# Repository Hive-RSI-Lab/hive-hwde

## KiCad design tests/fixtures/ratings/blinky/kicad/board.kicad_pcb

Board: 0 copper layers, 20 parts (0 on the bottom side), 12 nets, no tracks yet.

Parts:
C1, C2, C3, C9: 100nF 50V X7R; C0603
C4: 1uF 50V X5R; C0603
C5: 22uF 16V tantalum; CASE-B_3528
C6, C11: 10uF 25V X5R; C0805
C7, C8: 22pF 50V C0G; C0603
C10: 10nF 50V X7R; C0603
D1: SS34; SMA_L4.3-W2.6-LS5.2-RD
D2: Red 0805; LED0805-RD
J1: 1x2 2.54mm male THT; HDR-TH_2P-P2.54-V-M-3
J2: 1x4 2.54mm male THT; HDR-TH_4P-P2.54-V-M
R1: 1k; R0603
R2: 10k; R0603
U1: STM32F103C8T6; LQFP-48_L7.0-W7.0-P0.50-LS9.0-BL
U2: AMS1117-3.3; SOT-223-3_L6.5-W3.4-P2.30-LS7.0-BR
Y1: 8MHz 20pF; CRYSTAL-SMD_L11.5-W4.8-LS12.7

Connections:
+3V3: C1.1, C2.1, C3.1, C4.1, C5.1, C10.1, C11.1, J2.3, R1.1, U1.1, U1.9, U1.24, U1.36, U1.48, U2.2, U2.4
+5V: C6.1, D1.1, U2.3
/BOOT0: R2.1, U1.44
/LED: D2.1, U1.2
/LED_A: D2.2, R1.2
/NRST: C9.1, U1.7
/OSC_IN: C7.1, U1.5, Y1.1
/OSC_OUT: C8.1, U1.6, Y1.2
/SWCLK: J2.2, U1.37
/SWDIO: J2.1, U1.34
/VIN: D1.2, J1.1
GND: C1.2, C2.2, C3.2, C4.2, C5.2, C6.2, C7.2, C8.2, C9.2, C10.2, C11.2, J1.2, J2.4, R2.2, U1.8, U1.23, U1.35, U1.47, U2.1

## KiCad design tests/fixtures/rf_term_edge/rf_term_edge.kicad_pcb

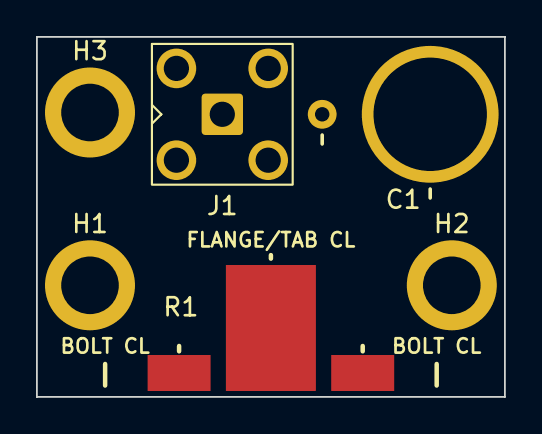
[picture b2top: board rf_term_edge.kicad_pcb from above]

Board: 2 copper layers, 26.0 x 20.0 mm, 6 parts (0 on the bottom side), 2 nets, no tracks yet.

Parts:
C1: 1-30pF; CAP-ADJ-TH_2P-BD7.5_5602
H1, H2, H3: M3; MountingHole_3.2mm_M3_Pad_5.0mm
J1: SMA; SMA_BAT_Wireless_BWSMA-KWE-Z001
R1: 50R 250W; R_LapPad_T50R0-250-12X

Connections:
/RF: C1.2, J1.1, R1.1
GND: C1.1, H1.1, H2.1, H3.1, J1.2, R1.2

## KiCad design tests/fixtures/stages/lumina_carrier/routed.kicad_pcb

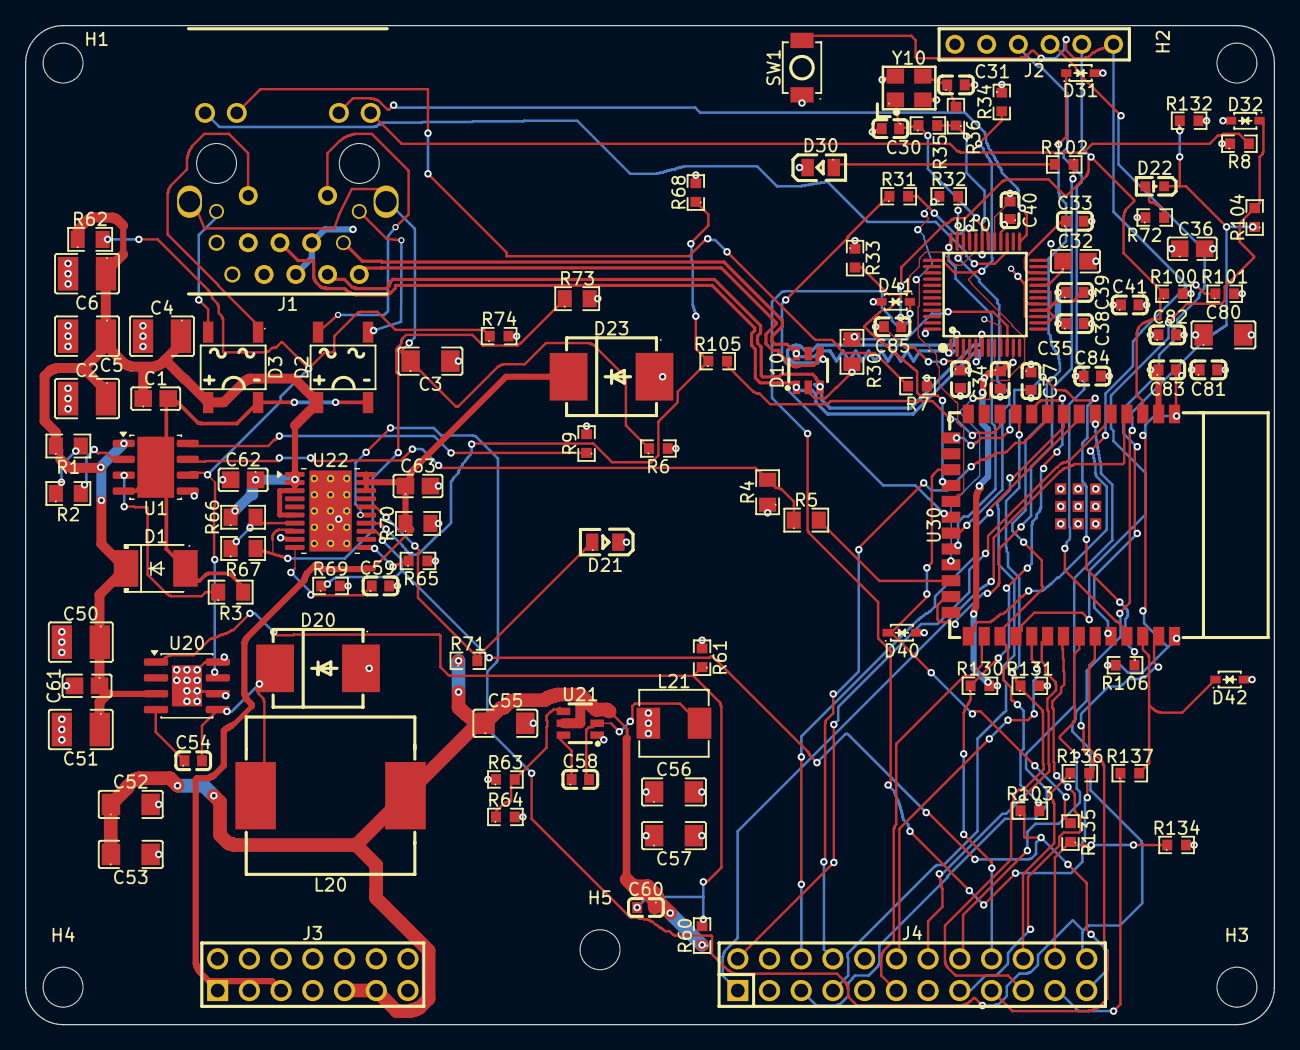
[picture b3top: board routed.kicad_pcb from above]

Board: 4 copper layers, 100.0 x 80.0 mm, 116 parts (0 on the bottom side), 85 nets.

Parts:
C1, C61, C62, C63: 100nF 100V X7R 0805; C0805
C2, C4, C5, C6: 10uF 100V X7R 1210; C1210
C3: 1nF 2kV X7R 1206; C1206
C30, C31: 27pF 50V NP0 0603; C0603
C32, C36: 4.7uF 25V X5R 0805; C0805
C33, C59: 10nF 50V X7R 0603; C0603
C34, C35, C37, C38, C39, C40, C41, C54, C58: 100nF 50V X7R 0603; C0603
C50, C51: 2.2uF 100V X7R 1210; C1210
C52, C53, C55, C56, C57: 22uF 25V X5R 1206; C1206
C60: 150pF 50V NP0 0603; C0603
C80: 22uF 25V X5R; C1206
C81, C82, C83: 100nF 50V X7R; C0603
C84, C85: 1uF 50V X5R; C0603
D1: SMBJ58A 58V 600W TVS; SMB_L4.3-W3.6-LS5.4-R-RD
D2: ABS210 2A 1000V bridge (Alt A); ABF_L5.1-W4.4-P4.00-LS6.2-BL
D3: ABS210 2A 1000V bridge (Alt B); ABF_L5.1-W4.4-P4.00-LS6.2-BL
D10: TPD4E1U06 4ch 0.55pF ESD array; SOT-23-6_L2.9-W1.6-P0.95-LS2.8-BR
D20, D23: SS510C 100V 5A Schottky SMC; SMC_L7.1-W6.2-LS8.1-R-RD
D21, D30: Green LED 0805; LED0805-R-RD
D22: Red LED 0603; LED-SMD_L1.6-W0.8-R-RD
D31, D32, D40, D41, D42: PESD3V3L1BA 3.3V ESD clamp SOD-323; SOD-323_L1.7-W1.3-LS2.6-BI
H1, H2, H3, H4, H5: MountingHole_3.2mm_M3
J1: LPJG0926HENL PoE+ RJ45 magjack; RJ45-TH_LPJG0926HENL_C22457393
J2: 1x6 2.54mm header (recovery); CONN-TH_DS1021-1X6SF11-B
J3: DS1021-2x7SF11-B 2x7 male header; HDR-TH_14P-P2.54-V-M-R2-C7-S2.54-1
J4: DS1021-2x12SF11-B 2x12 male header; HDR-TH_24P-P2.54-V-M-R2-C12-S2.54
L20: 68uH 3A 140mohm inductor; IND-SMD_L12.6-W13.5
L21: 4.7uH 4A 46mohm inductor; IND-SMD_L5.4-W5.2
R1, R2: 12.1k 1% 0805; R0805
R3: 90.9R 1% 0805; R0805
R4, R5: 10k 1% 0805; R0805
R6, R35: 1M 1% 0603; R0603
R7, R8, R72: 330R 1% 0603; R0603
R9, R36: 0R jumper 0603; R0603
R30: 12.4k 1% 0805; R0805
R31, R32: 22R 1% 0603; R0603
R33, R34, R64, R69, R71, R106, R132, R134: 10k 1% 0603; R0603
R60: 270k 1% 0603; R0603
R61, R68: 30k 1% 0603; R0603
R62, R70: 100k 1% 0805; R0805
R63: 33k 1% 0603; R0603
R65: 18k 1% 0603; R0603
R66: 620k 0.1% 0805; R0805
R67: 10k 0.1% 0805; R0805
R73: 12k 0.1% 0805; R0805
R74, R130, R131: 4.7k 1% 0603; R0603
R100, R101: 10k; R0603
R102: 330R; R0603
R103, R104, R105, R135, R136, R137: 1k 1% 0603; R0603
SW1: SMD tactile switch; SW-SMD_L3.9-W3.0-P4.45
U1: TPS2378DDAR; SOIC-8-1EP_3.9x4.9mm_P1.27mm_EP2.95x4.9mm_Mask2.71x3.4mm
U10: W5500; LQFP-48_L7.0-W7.0-P0.50-LS9.0-BL
U20: SCT2A25STER; SOIC-8-1EP_3.9x4.9mm_P1.27mm_EP2.41x3.3mm
U21: TPS563201DDCR; SOT-23-6_L2.9-W1.6-P0.95-LS2.8-BR
U22: TPS16630PWPR; HTSSOP-20-1EP_4.4x6.5mm_P0.65mm_EP3.4x6.5mm_Mask2.96x2.96mm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
U30: ESP32-S3-WROOM-1-N8; WIFIM-SMD_ESP32-S3-WROOM-1-N8
Y10: 25MHz 18pF CL crystal; OSC-SMD_4P-L3.2-W2.5-BL_SIT8008BI

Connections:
+3V3: C34.1, C35.1, C36.1, C37.1, C38.1, C39.1, C40.1, C41.1, C56.1, C57.1, C80.1, C81.1, C82.1, C83.1, C84.1, J1.4, J1.5, J2.2, J3.12, J3.14, L21.2, R4.1, R7.1, R8.1, R33.1, R34.1, R63.1, R72.1, R100.2, R101.2, R130.2, R131.2, R132.2, R134.2, U10.4, U10.8, U10.11, U10.15, U10.17, U10.21, U10.28, U30.2
+12V: C52.1, C53.1, C55.1, C60.1, J3.9, J3.11, L20.2, R60.1, R71.1, U21.3, U21.5
+48V_SW: C63.1, D23.2, J3.1, J3.3, J3.5, R70.1, U22.18, U22.19, U22.20
/ADC0: D41.1, R136.2, U30.39
/ADC1: D42.1, R137.2, U30.38
/CDB: R62.2, R74.1, U1.6, U20.7
/DSPI_CSn: J4.17, U30.35
/DSPI_MISO: J4.16, U30.34
/DSPI_MOSI: J4.15, U30.33
/DSPI_SCK: J4.14, U30.32
/ENABLE: J4.23, R69.1, R103.1, U22.13
/ETH_CSn: R33.2, U10.32, U30.18
/ETH_INTn: U10.36, U30.22
/ETH_LED_ACT: J1.18, U10.27
/ETH_LED_LINK: J1.16, U10.25
/ETH_MISO: U10.34, U30.21
/ETH_MOSI: R32.1, U30.19
/ETH_RSTn: R34.2, U10.37, U30.23
/ETH_RXN: D10.1, J1.6, U10.5
/ETH_RXP: D10.3, J1.3, U10.6
/ETH_SCLK: R31.1, U30.20
/ETH_TXN: D10.6, J1.2, U10.1
/ETH_TXP: D10.4, J1.1, U10.2
/FAULT: D22.2, J4.24, R104.1, R132.1, U22.15
/I2C_SCL: J4.18, R130.1, U30.10
/I2C_SDA: J4.19, R131.1, U30.11
/ID_ADC: D40.1, R135.2, U30.17
/IMON: R68.1, R105.1, U22.14
/PWM0: J4.1, U30.4
/PWM1: J4.2, U30.5
/PWM2: J4.5, U30.6
/PWM3: J4.6, U30.7
/PWM4: J4.7, U30.8
/PWM5: J4.8, U30.9
/PWM6: J4.11, U30.28
/PWM7: J4.12, U30.31
/T2P: R5.2, U30.24
/eth/1V2O: C33.1, U10.22
/eth/EXRES: R30.1, U10.10
/eth/MOSI_PHY: R32.2, U10.35
/eth/SCLK_PHY: R31.2, U10.33
/eth/TOCAP: C32.1, U10.20
/eth/XI: C30.1, R35.1, U10.30, Y10.1
/eth/XO: R35.2, R36.1, U10.31
/eth/XO_XTAL: C31.1, R36.2, Y10.3
/expansion/ADC0_CONN: J4.20, R136.1
/expansion/ADC1_CONN: J4.21, R137.1
/expansion/ID_ADC_CONN: J4.22, R134.1, R135.1
/mcu/BOOT: J2.6, R101.1, SW1.1, U30.27
/mcu/EN: C85.1, J2.5, R100.1, U30.3
/mcu/ENABLE_M: D31.1, R103.2, U30.29
/mcu/FAULT_M: D32.1, R104.2, U30.30
/mcu/IMON_M: R105.2, U30.12
/mcu/IO3_STRAP: R106.1, U30.15
/mcu/RXD0: J2.4, U30.36
/mcu/STATUS: R102.1, U30.25
/mcu/STATUS_A: D30.1, R102.2
/mcu/TXD0: J2.3, U30.37
/poe/APD: R9.1, U1.8
/poe/CLS: R3.1, U1.3
/poe/DEN: R2.2, U1.2
/poe/DEN_TAP: R1.2, R2.1
/poe/LED_G_A: J1.15, R8.2
/poe/LED_Y_A: J1.17, R7.2
/poe/POE_TAP_A1: D2.1, J1.11
/poe/POE_TAP_A2: D2.2, J1.12
/poe/POE_TAP_B1: D3.1, J1.13
/poe/POE_TAP_B2: D3.2, J1.14
/poe/SHIELD: C3.1, J1.19, J1.20, R6.1
/poe/T2P_OD: R4.2, R5.1, U1.7
/pwr/BST: C54.1, U20.4
/pwr/BST33: C58.1, U21.6
/pwr/DVDT: C59.1, U22.10
/pwr/FB33: R63.2, R64.1, U21.4
/pwr/FB48: C60.2, R60.2, R61.1, U20.1
/pwr/FLT_LED: D22.1, R72.2
/pwr/ILIM: R65.1, U22.11
/pwr/OVP: R67.2, R73.1, U22.8
/pwr/PGOOD: D21.1, R71.2, U22.16
/pwr/SW: C54.2, D20.2, L20.1, U20.5
/pwr/SW33: C58.2, L21.1, U21.2
/pwr/UVLO: R66.2, R67.1, U22.7
GND: C2.2, C3.2, C4.2, C5.2, C6.2, C30.2, C31.2, C32.2, C33.2, C34.2, C35.2, C36.2, C37.2, C38.2, C39.2, C40.2, C41.2, C50.2, C51.2, C52.2, C53.2, C55.2, C56.2, C57.2, C59.2, C61.2, C62.2, C63.2, C80.2, C81.2, C82.2, C83.2, C84.2, C85.2, D10.2, D20.1, D21.2, D23.1, D30.2, D31.2, D32.2, D40.2, D41.2, D42.2, J2.1, J3.2, J3.4, J3.6, J3.7, J3.8, J3.10, J3.13, J4.3, J4.4, J4.9, J4.10, J4.13, R6.2, R9.2, R30.2, R61.2, R64.2, R65.2, R68.2, R69.2, R70.2, R73.2, R74.2, R106.2, SW1.2, U1.5, U10.3, U10.9, U10.14, U10.16, U10.19, U10.23, U10.29, U10.48, U20.6, U20.8, U20.9, U21.1, U22.9, U22.21, U30.1, U30.40, U30.41, Y10.2, Y10.4
V48_RAW: C1.1, C2.1, C4.1, C5.1, C6.1, C50.1, C51.1, C61.1, C62.1, D1.2, D2.3, D3.3, R1.1, R62.1, R66.1, U1.1, U20.3, U22.1, U22.2, U22.3, U22.6
V48_RTN: C1.2, D1.1, D2.4, D3.4, R3.2, U1.4, U1.9

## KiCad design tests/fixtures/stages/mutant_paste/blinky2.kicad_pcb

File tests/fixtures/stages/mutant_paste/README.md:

# mutant_paste - tented-pad gerber mutant (dfm_pad_tented known answer)

Copied 2026-08-06 from tests/fixtures/stages/mutant_cpl/gerbers (blinky2
cpl-rotation mutant export, kicad-cli 10.0.3), then ONE mask-opening flash
deleted from blinky2-F_Mask.gts: `X118400000Y-129625000D03*` (C8 pad 1,
board space ~(118.4, 129.625)). Its solder-paste aperture in
blinky2-F_Paste.gtp is untouched, so dfm_check.check_pad_tented must report
exactly one dfm_pad_tented ERROR there (and the inherited cpl_polarity D1
error stays). Board file: blinky2.kicad_pcb (the cpl-rotation mutant);
polarity oracle: tests/s7_regen/blinky2/golden.net.

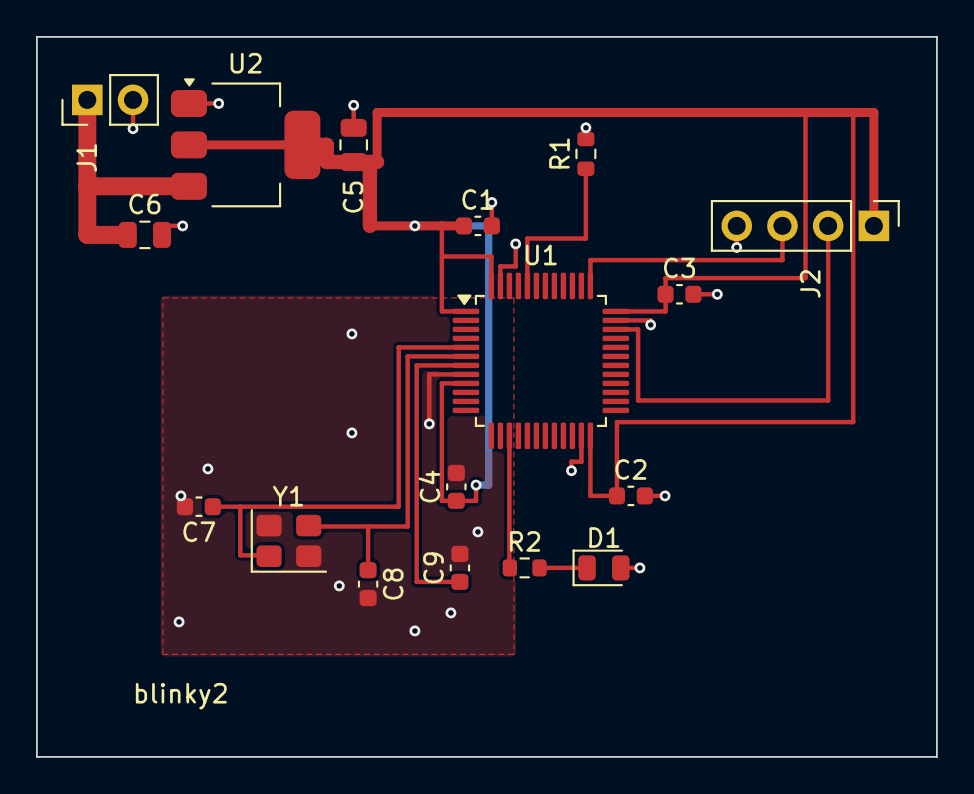
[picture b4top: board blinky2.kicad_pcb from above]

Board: 2 copper layers, 50.0 x 40.0 mm, 17 parts (0 on the bottom side), 11 nets.

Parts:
C1, C2, C3, C4, C9: 100nF; C_0603_1608Metric
C5, C6: 10uF; C_0805_2012Metric
C7, C8: 22pF; C_0603_1608Metric
D1: LED_red; LED_0805_2012Metric
J1: PWR_5V; PinHeader_1x02_P2.54mm_Vertical
J2: SWD; PinHeader_1x04_P2.54mm_Vertical
R1: 10k; R_0603_1608Metric
R2: 470; R_0603_1608Metric
U1: STM32F103C8T6; LQFP-48_7x7mm_P0.5mm
U2: AMS1117-3.3; SOT-223-3_TabPin2
Y1: 8MHz; Crystal_SMD_3225-4Pin_3.2x2.5mm

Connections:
+3V3: C1.1, C2.1, C3.1, C4.1, C5.1, J2.1, U1.1, U1.9, U1.24, U1.36, U1.48, U2.2
+5V: C6.1, J1.1, U2.3
/BOOT0: R1.1, U1.44
/LED: R2.1, U1.15
/LED_A: D1.1, R2.2
/NRST: C9.1, U1.7
/OSC_IN: C7.1, U1.5, Y1.1
/OSC_OUT: C8.1, U1.6, Y1.3
/SWCLK: J2.3, U1.37
/SWDIO: J2.2, U1.34
GND: C1.2, C2.2, C3.2, C4.2, C5.2, C6.2, C7.2, C8.2, C9.2, D1.2, J1.2, J2.4, R1.2, U1.8, U1.23, U1.35, U1.47, U2.1, Y1.2, Y1.4
